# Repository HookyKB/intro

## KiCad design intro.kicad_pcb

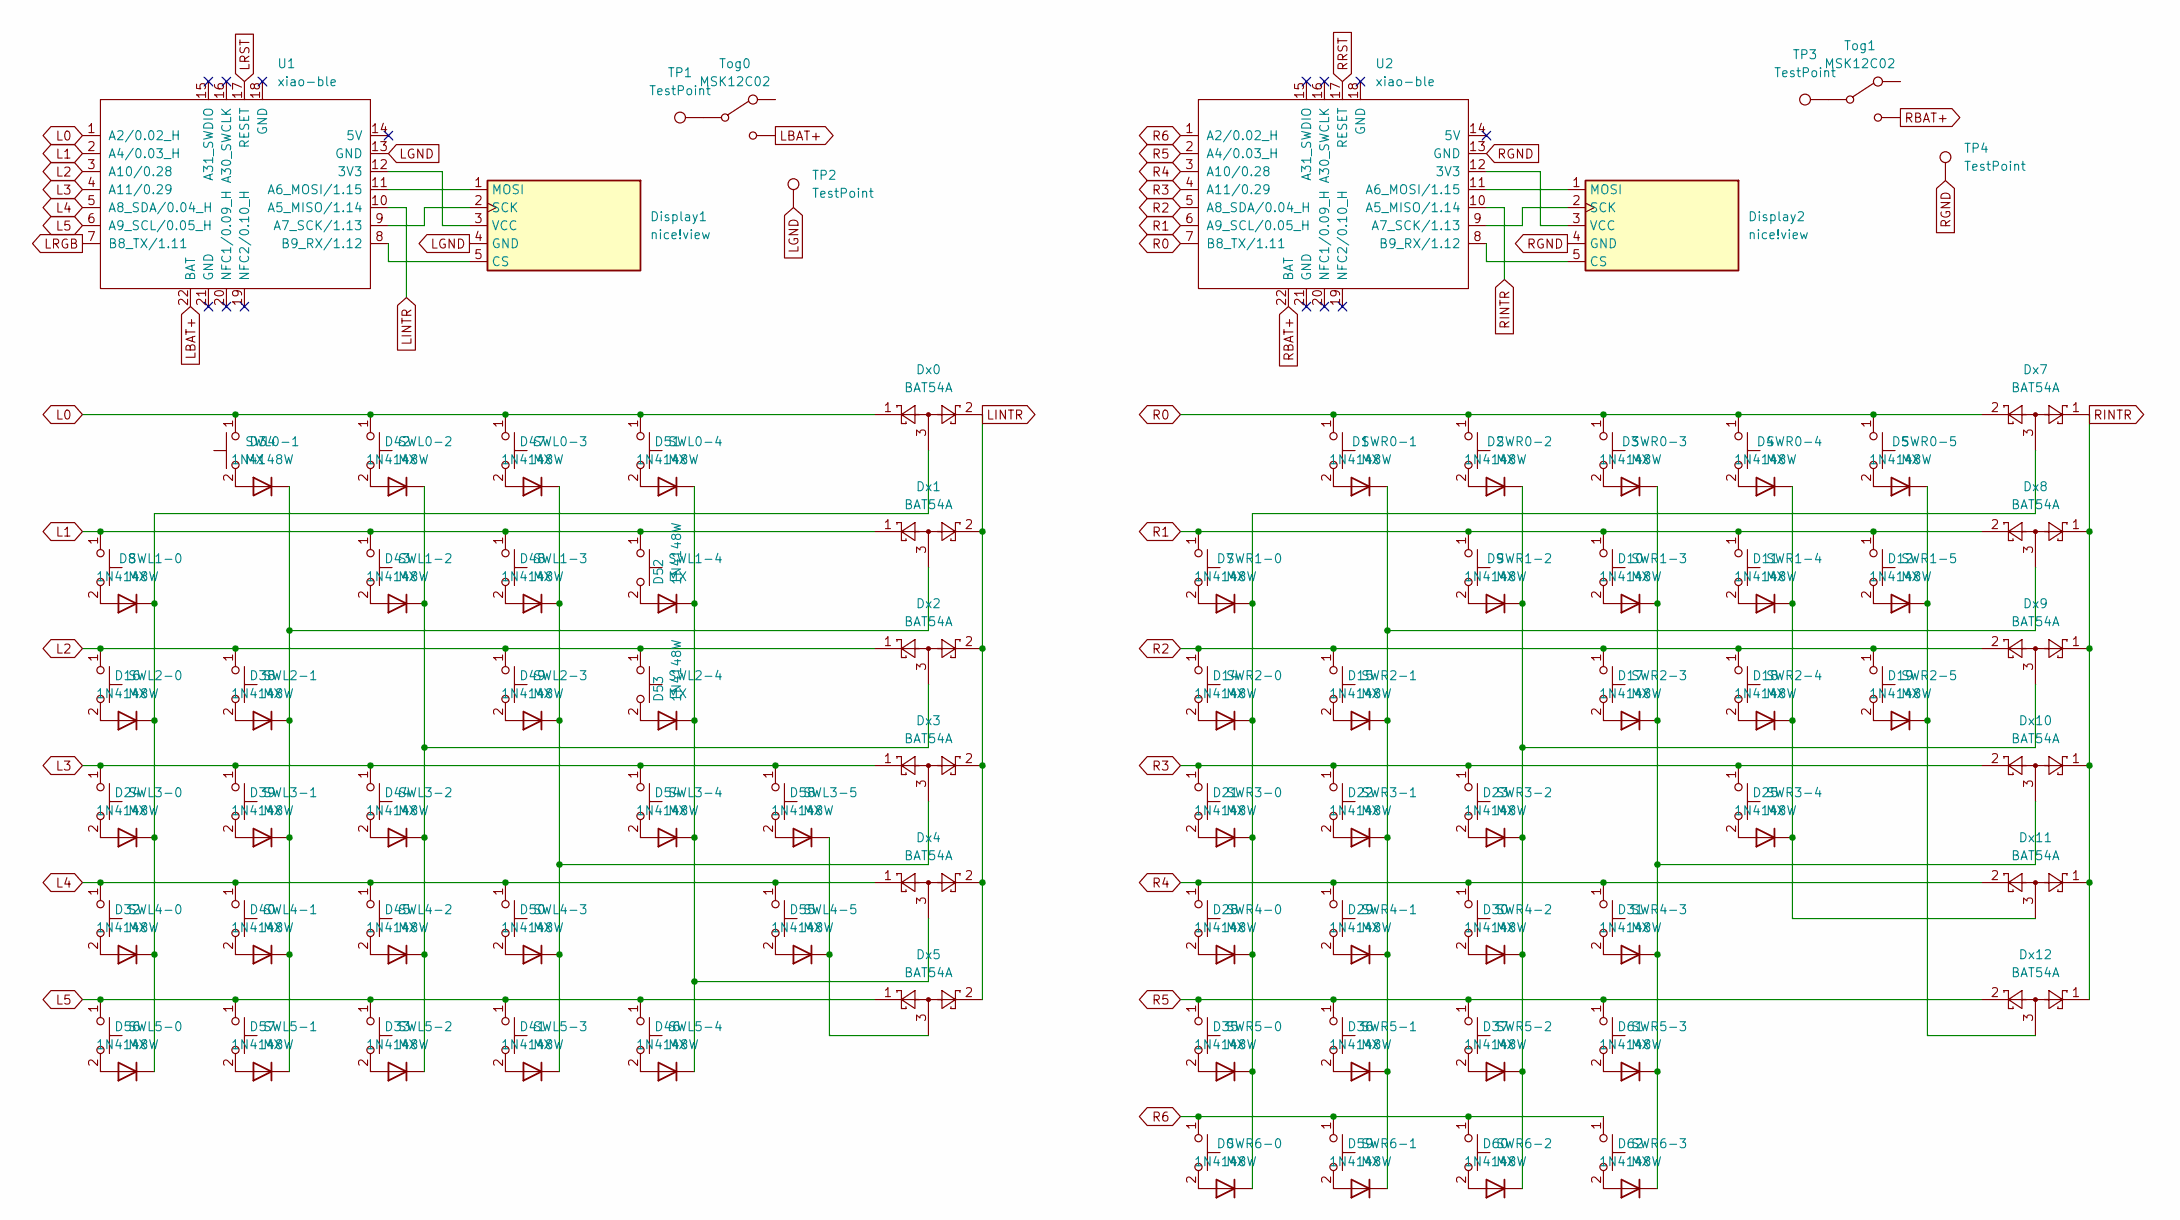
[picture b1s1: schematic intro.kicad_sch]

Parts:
D0, D1, D2, D3, D4, D5, D7, D8, D9, D10, D11, D12, D14, D15, D16, D17, D18, D19, D21, D22, D23, D24, D25, D28, D29, D30, D31, D32, D33, D34, D35, D36, D37, D38, D39, D40, D41, D42, D43, D44, D45, D46, D47, D48, D49, D50, D51, D52, D53, D54, D55, D56, D57, D58, D59, D60, D61, D62: 1N4148W; D_SOD-123
Display1, Display2: nice!view; nice_view
Dx0, Dx1, Dx2, Dx3, Dx4, Dx5, Dx7, Dx8, Dx9, Dx10, Dx11, Dx12: BAT54A; SOD_T
SWL0-1, SWL0-2, SWL0-3, SWL0-4, SWL1-0, SWL1-2, SWL1-3, SWL1-4, SWL2-0, SWL2-1, SWL2-3, SWL2-4, SWL3-0, SWL3-1, SWL3-2, SWL3-4, SWL3-5, SWL4-0, SWL4-1, SWL4-2, SWL4-3, SWL4-5, SWL5-0, SWL5-1, SWL5-2, SWL5-3, SWL5-4: MX; SW_MX_HS_1u
SWR0-1, SWR0-2, SWR0-3, SWR0-4, SWR0-5, SWR1-0, SWR1-2, SWR1-3, SWR1-4, SWR1-5, SWR2-0, SWR2-1, SWR2-3, SWR2-4, SWR2-5, SWR3-0, SWR3-1, SWR3-2, SWR3-4, SWR4-0, SWR4-1, SWR4-2, SWR4-3, SWR5-0, SWR5-1, SWR5-2, SWR5-3, SWR6-0, SWR6-1, SWR6-2, SWR6-3: MX; SW_MX_HS_1u
TP1, TP2, TP3, TP4: TestPoint; pogo
Tog0, Tog1: MSK12C02; MSK-12C02
U1, U2: xiao-ble; xiao

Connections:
L0: Dx0.1, SWL0-1.1, SWL0-2.1, SWL0-3.1, SWL0-4.1, U1.1 (A2/0.02_H)
L1: Dx1.1, SWL1-0.1, SWL1-2.1, SWL1-3.1, SWL1-4.1, U1.2 (A4/0.03_H)
L2: Dx2.1, SWL2-0.1, SWL2-1.1, SWL2-3.1, SWL2-4.1, U1.3 (A10/0.28)
L3: Dx3.1, SWL3-0.1, SWL3-1.1, SWL3-2.1, SWL3-4.1, SWL3-5.1, U1.4 (A11/0.29)
L4: Dx4.1, SWL4-0.1, SWL4-1.1, SWL4-2.1, SWL4-3.1, SWL4-5.1, U1.5 (A8_SDA/0.04_H)
L5: Dx5.1, SWL5-0.1, SWL5-1.1, SWL5-2.1, SWL5-3.1, SWL5-4.1, U1.6 (A9_SCL/0.05_H)
LBAT+: Tog0.3, U1.22 (BAT)
LGND: Display1.4 (GND), TP2.1, U1.13 (GND)
LINTR: Dx0.2, Dx1.2, Dx2.2, Dx3.2, Dx4.2, Dx5.2, U1.10 (A5_MISO/1.14)
LRGB: U1.7 (B8_TX/1.11)
unnamed: D0.1 (K), D7.1 (K), D14.1 (K), D21.1 (K), D28.1 (K), D35.1 (K), Dx7.3
unnamed: D0.2 (A), SWR6-0.2
unnamed: D1.1 (K), D15.1 (K), D22.1 (K), D29.1 (K), D36.1 (K), D59.1 (K), Dx8.3
unnamed: D1.2 (A), SWR0-1.2
unnamed: D2.1 (K), D9.1 (K), D23.1 (K), D30.1 (K), D37.1 (K), D60.1 (K), Dx9.3
unnamed: D2.2 (A), SWR0-2.2
unnamed: D3.2 (A), SWR0-3.2
unnamed: D4.2 (A), SWR0-4.2
unnamed: D5.2 (A), SWR0-5.2
unnamed: D7.2 (A), SWR1-0.2
unnamed: D8.2 (A), SWL1-0.2
unnamed: D9.2 (A), SWR1-2.2
unnamed: D3.1 (K), D10.1 (K), D17.1 (K), D31.1 (K), D61.1 (K), D62.1 (K), Dx10.3
unnamed: D10.2 (A), SWR1-3.2
unnamed: D4.1 (K), D11.1 (K), D18.1 (K), D25.1 (K), Dx11.3
unnamed: D11.2 (A), SWR1-4.2
unnamed: D5.1 (K), D12.1 (K), D19.1 (K), Dx12.3
unnamed: D12.2 (A), SWR1-5.2
unnamed: D14.2 (A), SWR2-0.2
unnamed: D15.2 (A), SWR2-1.2
unnamed: D8.1 (K), D16.1 (K), D24.1 (K), D32.1 (K), D56.1 (K), Dx0.3
unnamed: D16.2 (A), SWL2-0.2
unnamed: D17.2 (A), SWR2-3.2
unnamed: D18.2 (A), SWR2-4.2
unnamed: D19.2 (A), SWR2-5.2
unnamed: D21.2 (A), SWR3-0.2
unnamed: D22.2 (A), SWR3-1.2
unnamed: D23.2 (A), SWR3-2.2
unnamed: D24.2 (A), SWL3-0.2
unnamed: D25.2 (A), SWR3-4.2
unnamed: D28.2 (A), SWR4-0.2
unnamed: D29.2 (A), SWR4-1.2
unnamed: D30.2 (A), SWR4-2.2
unnamed: D31.2 (A), SWR4-3.2
unnamed: D32.2 (A), SWL4-0.2
unnamed: D33.1 (K), D42.1 (K), D43.1 (K), D44.1 (K), D45.1 (K), Dx2.3
unnamed: D33.2 (A), SWL5-2.2
unnamed: D34.1 (K), D38.1 (K), D39.1 (K), D40.1 (K), D57.1 (K), Dx1.3
unnamed: D34.2 (A), SWL0-1.2
unnamed: D35.2 (A), SWR5-0.2
unnamed: D36.2 (A), SWR5-1.2
unnamed: D37.2 (A), SWR5-2.2
unnamed: D38.2 (A), SWL2-1.2
unnamed: D39.2 (A), SWL3-1.2
unnamed: D40.2 (A), SWL4-1.2
unnamed: D41.1 (K), D47.1 (K), D48.1 (K), D49.1 (K), D50.1 (K), Dx3.3
unnamed: D41.2 (A), SWL5-3.2
unnamed: D42.2 (A), SWL0-2.2
unnamed: D43.2 (A), SWL1-2.2
unnamed: D44.2 (A), SWL3-2.2
unnamed: D45.2 (A), SWL4-2.2
unnamed: D46.1 (K), D51.1 (K), D52.1 (K), D53.1 (K), D54.1 (K), Dx4.3
unnamed: D46.2 (A), SWL5-4.2
unnamed: D47.2 (A), SWL0-3.2
unnamed: D48.2 (A), SWL1-3.2
unnamed: D49.2 (A), SWL2-3.2
unnamed: D50.2 (A), SWL4-3.2
unnamed: D51.2 (A), SWL0-4.2
unnamed: D52.2 (A), SWL1-4.2
unnamed: D53.2 (A), SWL2-4.2
unnamed: D54.2 (A), SWL3-4.2
unnamed: D55.1 (K), D58.1 (K), Dx5.3
unnamed: D55.2 (A), SWL4-5.2
unnamed: D56.2 (A), SWL5-0.2
unnamed: D57.2 (A), SWL5-1.2
unnamed: D58.2 (A), SWL3-5.2
unnamed: D59.2 (A), SWR6-1.2
unnamed: D60.2 (A), SWR6-2.2
unnamed: D61.2 (A), SWR5-3.2
unnamed: D62.2 (A), SWR6-3.2
unnamed: Display1.1 (MOSI), U1.11 (A6_MOSI/1.15)
unnamed: Display1.2 (SCK), U1.9 (A7_SCK/1.13)
unnamed: Display1.3 (VCC), U1.12 (3V3)
unnamed: Display1.5 (CS), U1.8 (B9_RX/1.12)
unnamed: Display2.1 (MOSI), U2.11 (A6_MOSI/1.15)
unnamed: Display2.2 (SCK), U2.9 (A7_SCK/1.13)
unnamed: Display2.3 (VCC), U2.12 (3V3)
unnamed: Display2.5 (CS), U2.8 (B9_RX/1.12)
unnamed: TP1.1, Tog0.2
unnamed: TP3.1, Tog1.2
R0: Dx7.2, SWR0-1.1, SWR0-2.1, SWR0-3.1, SWR0-4.1, SWR0-5.1, U2.7 (B8_TX/1.11)
R1: Dx8.2, SWR1-0.1, SWR1-2.1, SWR1-3.1, SWR1-4.1, SWR1-5.1, U2.6 (A9_SCL/0.05_H)
R2: Dx9.2, SWR2-0.1, SWR2-1.1, SWR2-3.1, SWR2-4.1, SWR2-5.1, U2.5 (A8_SDA/0.04_H)
R3: Dx10.2, SWR3-0.1, SWR3-1.1, SWR3-2.1, SWR3-4.1, U2.4 (A11/0.29)
R4: Dx11.2, SWR4-0.1, SWR4-1.1, SWR4-2.1, SWR4-3.1, U2.3 (A10/0.28)
R5: Dx12.2, SWR5-0.1, SWR5-1.1, SWR5-2.1, SWR5-3.1, U2.2 (A4/0.03_H)
R6: SWR6-0.1, SWR6-1.1, SWR6-2.1, SWR6-3.1, U2.1 (A2/0.02_H)
RBAT+: Tog1.3, U2.22 (BAT)
RGND: Display2.4 (GND), TP4.1, U2.13 (GND)
RINTR: Dx7.1, Dx8.1, Dx9.1, Dx10.1, Dx11.1, Dx12.1, U2.10 (A5_MISO/1.14)

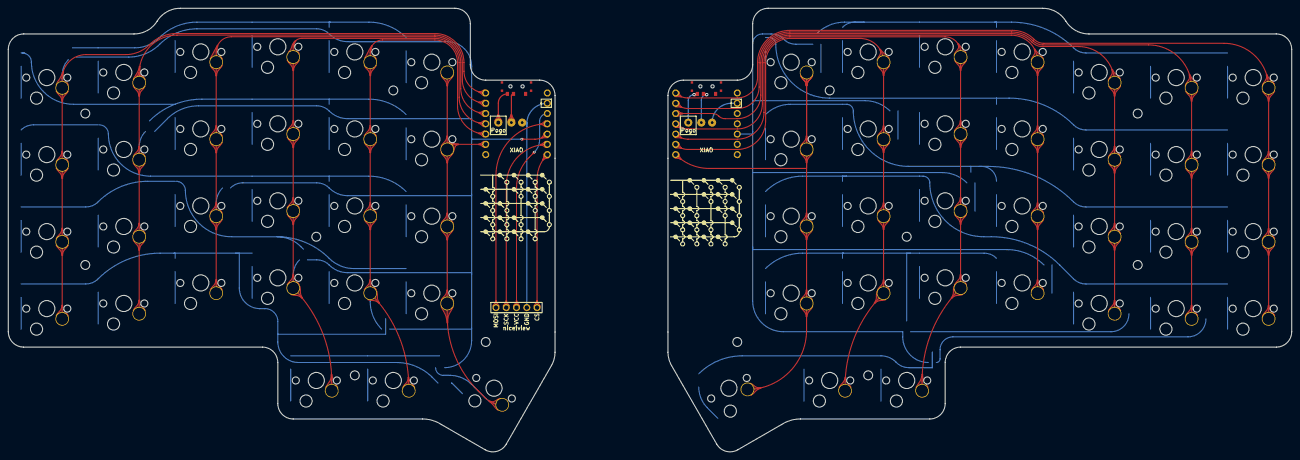
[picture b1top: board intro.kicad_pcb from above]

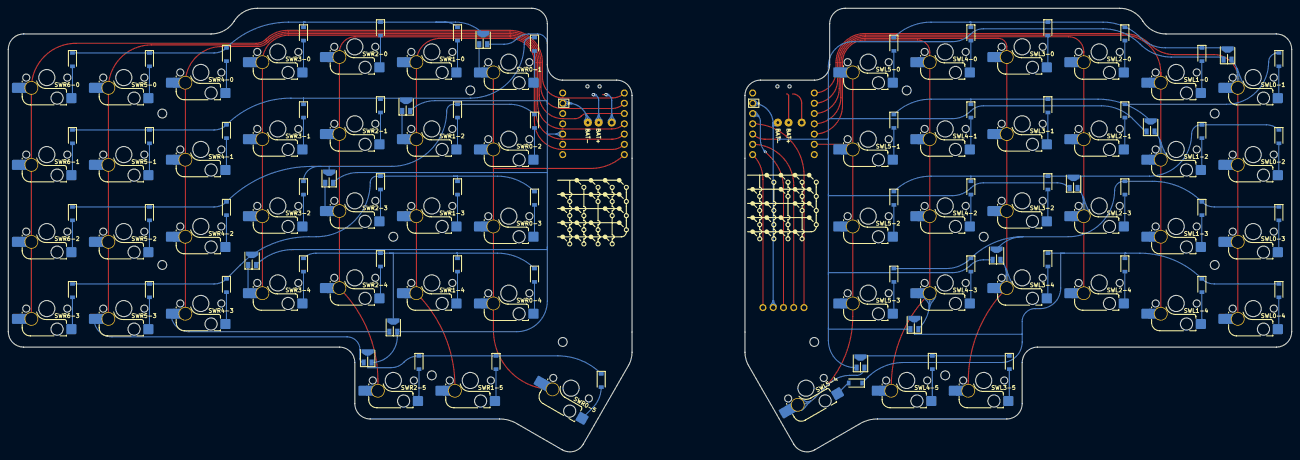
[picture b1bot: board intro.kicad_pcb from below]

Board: 2 copper layers, 317.5 x 109.7 mm, 137 parts (74 on the bottom side), 95 nets.

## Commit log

2023-04-08 initial
